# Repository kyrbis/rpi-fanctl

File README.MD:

This is a replacement pcb for the [ElectroCookie Raspberry Pi 4 Case, Aluminum Mini Tower Case](https://www.amazon.de/dp/B09R6TZCQ8) (or probably [this one](https://www.amazon.de/dp/B09QG349ZL)) to be used with PWM controlled 5V fans like [noctua NF-A4x10 5V PWM, 4-Pin](https://www.amazon.de/dp/B07DXS86G7).

You might also need a [3D printed fan adapter](https://www.thingiverse.com/thing:2995904).

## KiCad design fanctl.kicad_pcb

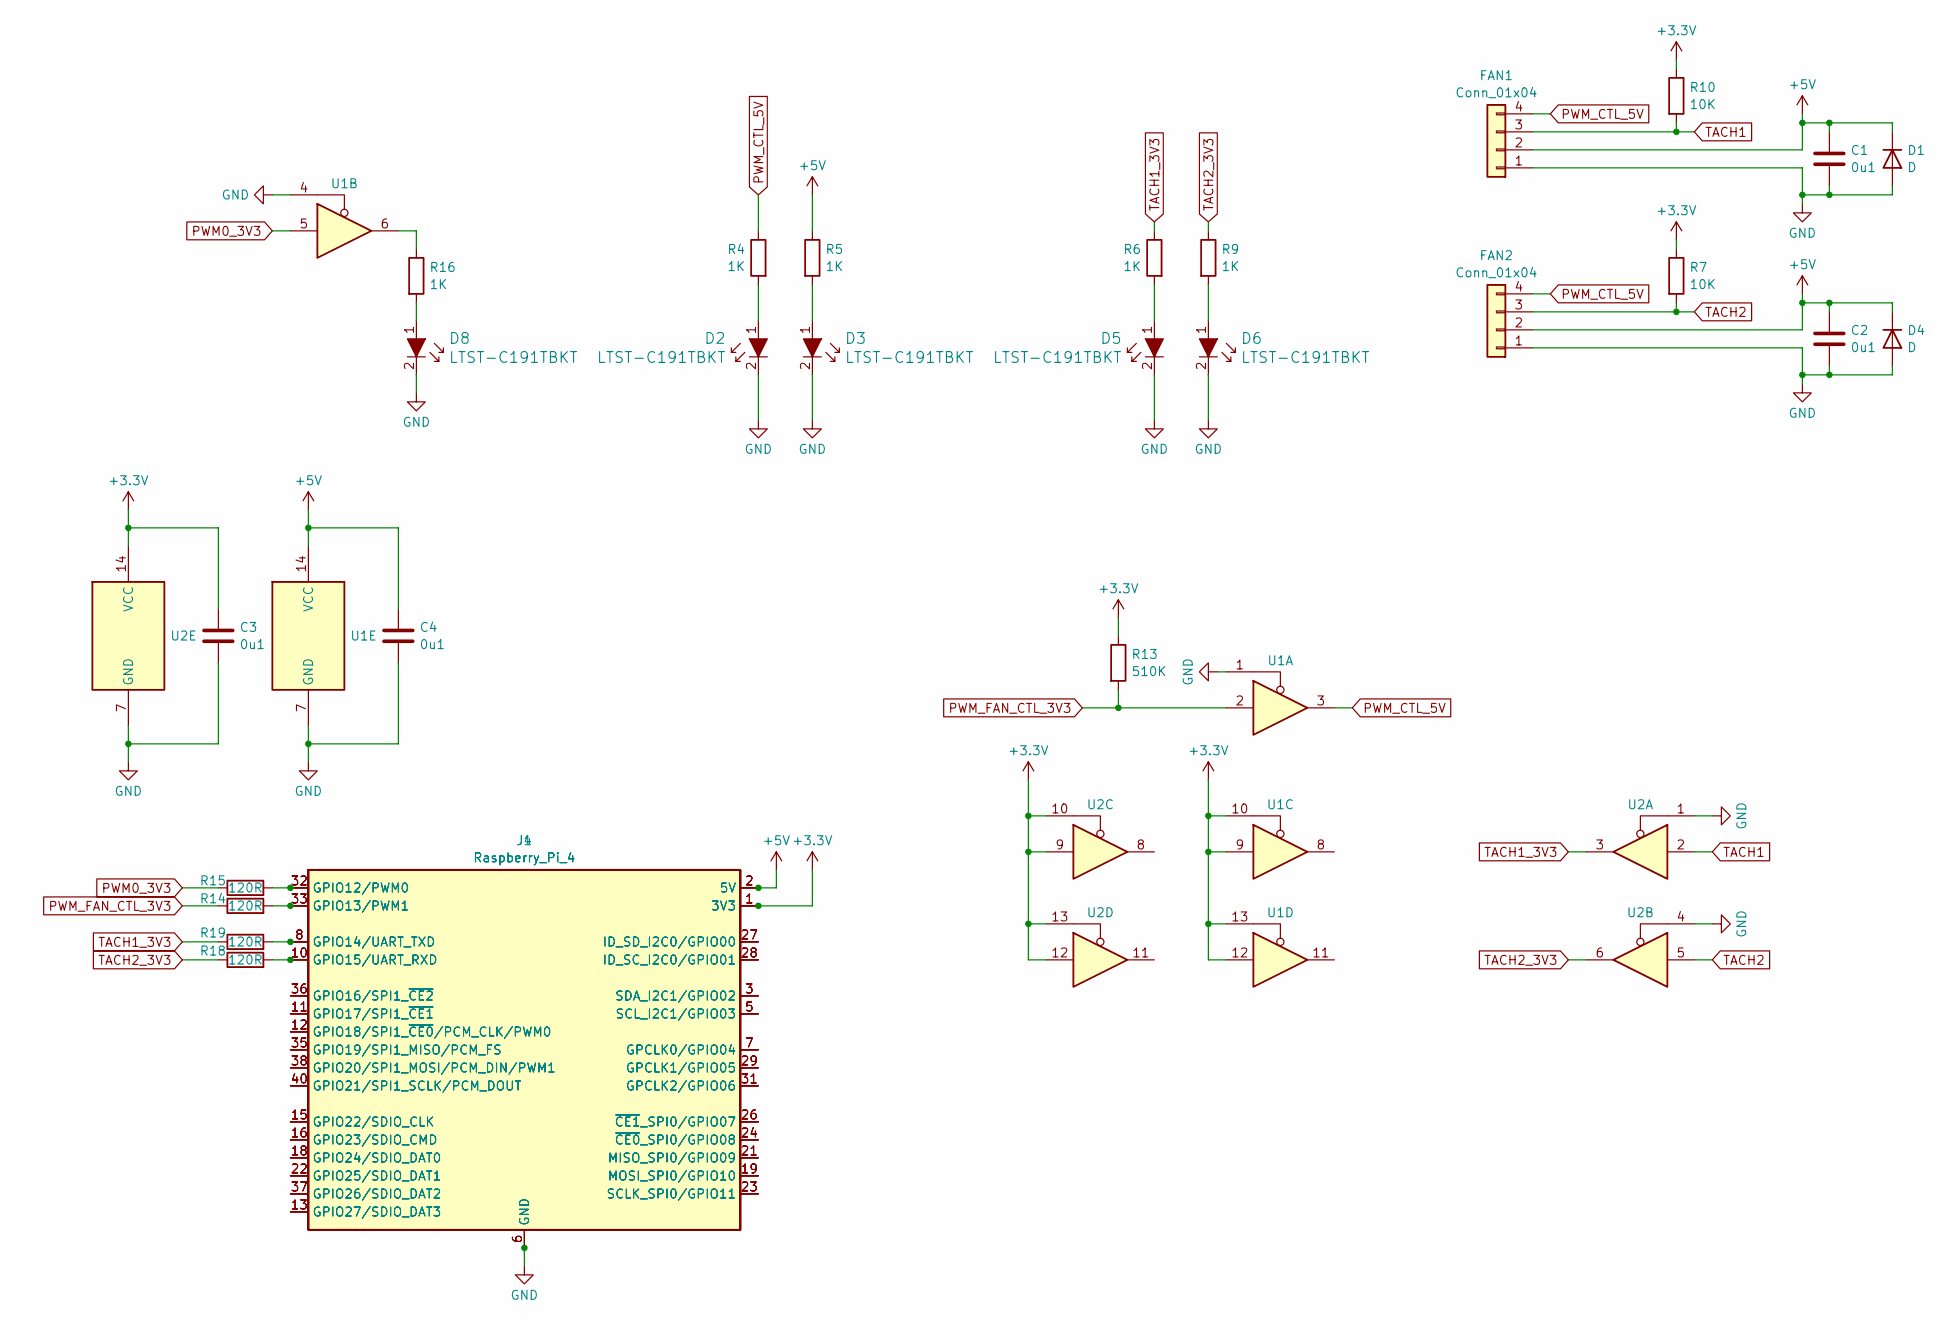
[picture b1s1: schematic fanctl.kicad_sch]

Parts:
C1, C2, C3, C4: 0u1; C_0805_2012Metric
D1: D; D_SOD-123F
D2, D3, D5, D6, D8: LTST-C191TBKT; D_0402_1005Metric_Pad0.77x0.64mm_HandSolder; MPN LTST-C191TBKT; Digi-Key_PN 160-1647-1-ND
D4: D; D_SOD-123
FAN1, FAN2: Conn_01x04; PinHeader_1x04_P2.54mm_Horizontal
J1: Raspberry_Pi_4; PinSocket_2x20_P2.54mm_Horizontal
J4: Raspberry_Pi_4; PinHeader_2x20_P2.54mm_Vertical
R4, R5, R6, R9, R16: 1K; R_0603_1608Metric_Pad0.98x0.95mm_HandSolder
R7, R10: 10K; R_0603_1608Metric_Pad0.98x0.95mm_HandSolder
R13: 510K; R_0603_1608Metric_Pad0.98x0.95mm_HandSolder
R14, R15, R18, R19: 120R; R_0603_1608Metric_Pad0.98x0.95mm_HandSolder
U1, U2: SN74HCT125DR; SOIC-14_3.9x8.7mm_P1.27mm

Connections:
+3.3V: C3.1, J1.1 (3V3), J1.17 (3V3), J4.1 (3V3), J4.17 (3V3), R7.1, R10.1, R13.1, U1.9, U1.10, U1.12, U1.13, U2.9, U2.10, U2.12, U2.13, U2.14 (VCC)
+5V: C1.1, C2.1, C4.1, D1.1 (K), D4.1 (K), FAN1.2, FAN2.2, J1.2 (5V), J1.4 (5V), J4.2 (5V), J4.4 (5V), R5.1, U1.14 (VCC)
GND: C1.2, C2.2, C3.2, C4.2, D1.2 (A), D2.2, D3.2, D4.2 (A), D5.2, D6.2, D8.2, FAN1.1, FAN2.1, J1.6 (GND), J1.9 (GND), J1.14 (GND), J1.20 (GND), J1.25 (GND), J1.30 (GND), J1.34 (GND), J1.39 (GND), J4.6 (GND), J4.9 (GND), J4.14 (GND), J4.20 (GND), J4.25 (GND), J4.30 (GND), J4.34 (GND), J4.39 (GND), U1.1, U1.4, U1.7 (GND), U2.1, U2.4, U2.7 (GND)
unnamed: D2.1, R4.2
unnamed: D3.1, R5.2
unnamed: D5.1, R6.2
unnamed: D6.1, R9.2
unnamed: D8.1, R16.2
unnamed: J1.7 (GPCLK0/GPIO04), J4.7 (GPCLK0/GPIO04)
unnamed: J1.29 (GPCLK1/GPIO05), J4.29 (GPCLK1/GPIO05)
unnamed: J1.31 (GPCLK2/GPIO06), J4.31 (GPCLK2/GPIO06)
unnamed: J1.32 (GPIO12/PWM0), J4.32 (GPIO12/PWM0), R15.2
unnamed: J1.33 (GPIO13/PWM1), J4.33 (GPIO13/PWM1), R14.2
unnamed: J1.8 (GPIO14/UART_TXD), J4.8 (GPIO14/UART_TXD), R19.2
unnamed: J1.10 (GPIO15/UART_RXD), J4.10 (GPIO15/UART_RXD), R18.2
unnamed: J1.36 (GPIO16/SPI1_~CE2), J4.36 (GPIO16/SPI1_~CE2)
unnamed: J1.11 (GPIO17/SPI1_~CE1), J4.11 (GPIO17/SPI1_~CE1)
unnamed: J1.12 (GPIO18/SPI1_~CE0/PCM_CLK/PWM0), J4.12 (GPIO18/SPI1_~CE0/PCM_CLK/PWM0)
unnamed: J1.35 (GPIO19/SPI1_MISO/PCM_FS), J4.35 (GPIO19/SPI1_MISO/PCM_FS)
unnamed: J1.38 (GPIO20/SPI1_MOSI/PCM_DIN/PWM1), J4.38 (GPIO20/SPI1_MOSI/PCM_DIN/PWM1)
unnamed: J1.40 (GPIO21/SPI1_SCLK/PCM_DOUT), J4.40 (GPIO21/SPI1_SCLK/PCM_DOUT)
unnamed: J1.15 (GPIO22/SDIO_CLK), J4.15 (GPIO22/SDIO_CLK)
unnamed: J1.16 (GPIO23/SDIO_CMD), J4.16 (GPIO23/SDIO_CMD)
unnamed: J1.18 (GPIO24/SDIO_DAT0), J4.18 (GPIO24/SDIO_DAT0)
unnamed: J1.22 (GPIO25/SDIO_DAT1), J4.22 (GPIO25/SDIO_DAT1)
unnamed: J1.37 (GPIO26/SDIO_DAT2), J4.37 (GPIO26/SDIO_DAT2)
unnamed: J1.13 (GPIO27/SDIO_DAT3), J4.13 (GPIO27/SDIO_DAT3)
unnamed: J1.28 (ID_SC_I2C0/GPIO01), J4.28 (ID_SC_I2C0/GPIO01)
unnamed: J1.27 (ID_SD_I2C0/GPIO00), J4.27 (ID_SD_I2C0/GPIO00)
unnamed: J1.21 (MISO_SPI0/GPIO09), J4.21 (MISO_SPI0/GPIO09)
unnamed: J1.19 (MOSI_SPI0/GPIO10), J4.19 (MOSI_SPI0/GPIO10)
unnamed: J1.23 (SCLK_SPI0/GPIO11), J4.23 (SCLK_SPI0/GPIO11)
unnamed: J1.5 (SCL_I2C1/GPIO03), J4.5 (SCL_I2C1/GPIO03)
unnamed: J1.3 (SDA_I2C1/GPIO02), J4.3 (SDA_I2C1/GPIO02)
unnamed: J1.24 (~CE0_SPI0/GPIO08), J4.24 (~CE0_SPI0/GPIO08)
unnamed: J1.26 (~CE1_SPI0/GPIO07), J4.26 (~CE1_SPI0/GPIO07)
unnamed: R16.1, U1.6
PWM0_3V3: R15.1, U1.5
PWM_CTL_5V: FAN1.4, FAN2.4, R4.1, U1.3
PWM_FAN_CTL_3V3: R13.2, R14.1, U1.2
TACH1: FAN1.3, R10.2, U2.2
TACH1_3V3: R6.1, R19.1, U2.3
TACH2: FAN2.3, R7.2, U2.5
TACH2_3V3: R9.1, R18.1, U2.6

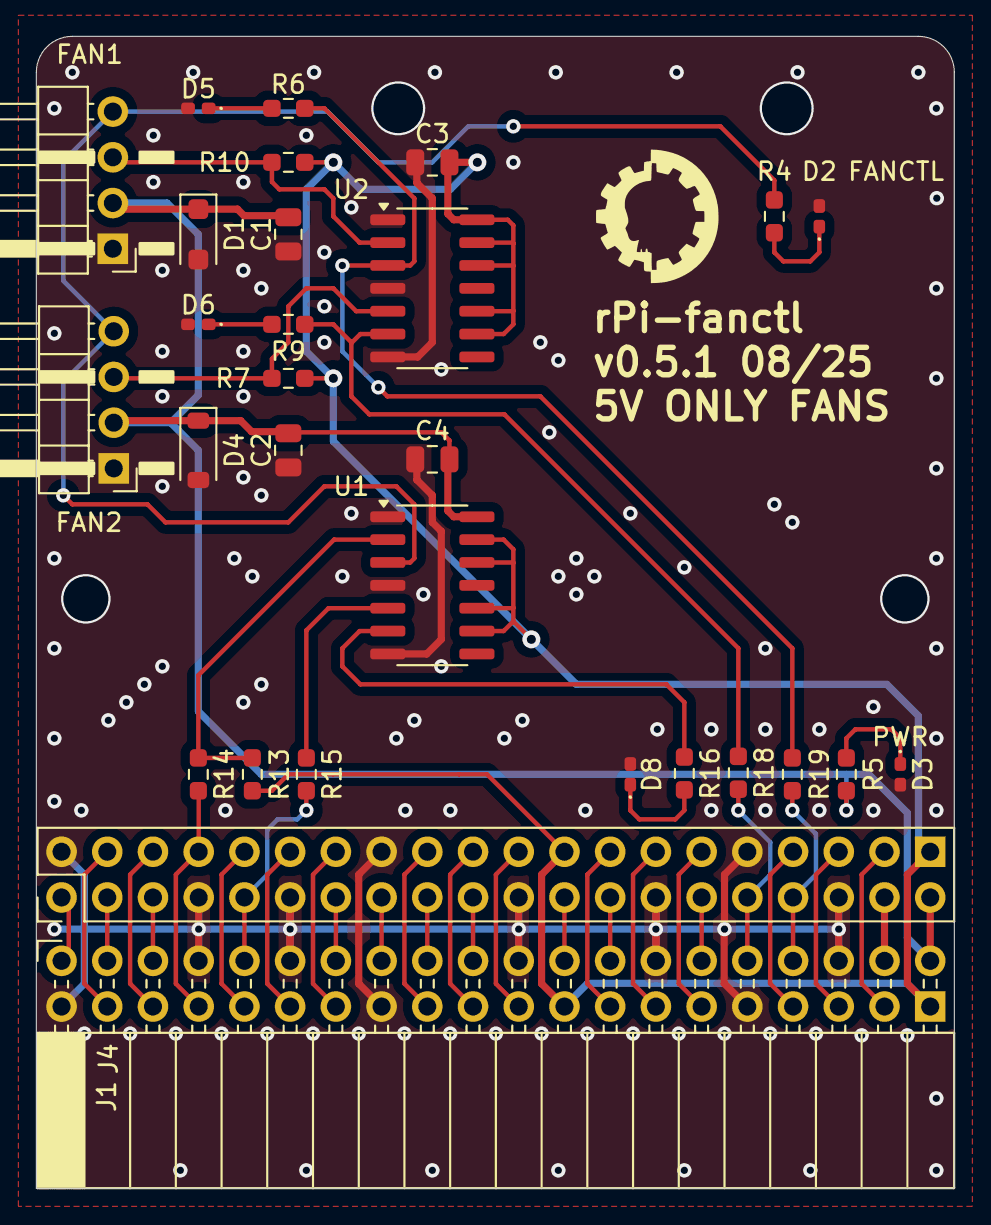
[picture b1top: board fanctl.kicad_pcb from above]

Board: 4 copper layers, 51.0 x 64.0 mm, 29 parts (0 on the bottom side), 44 nets.

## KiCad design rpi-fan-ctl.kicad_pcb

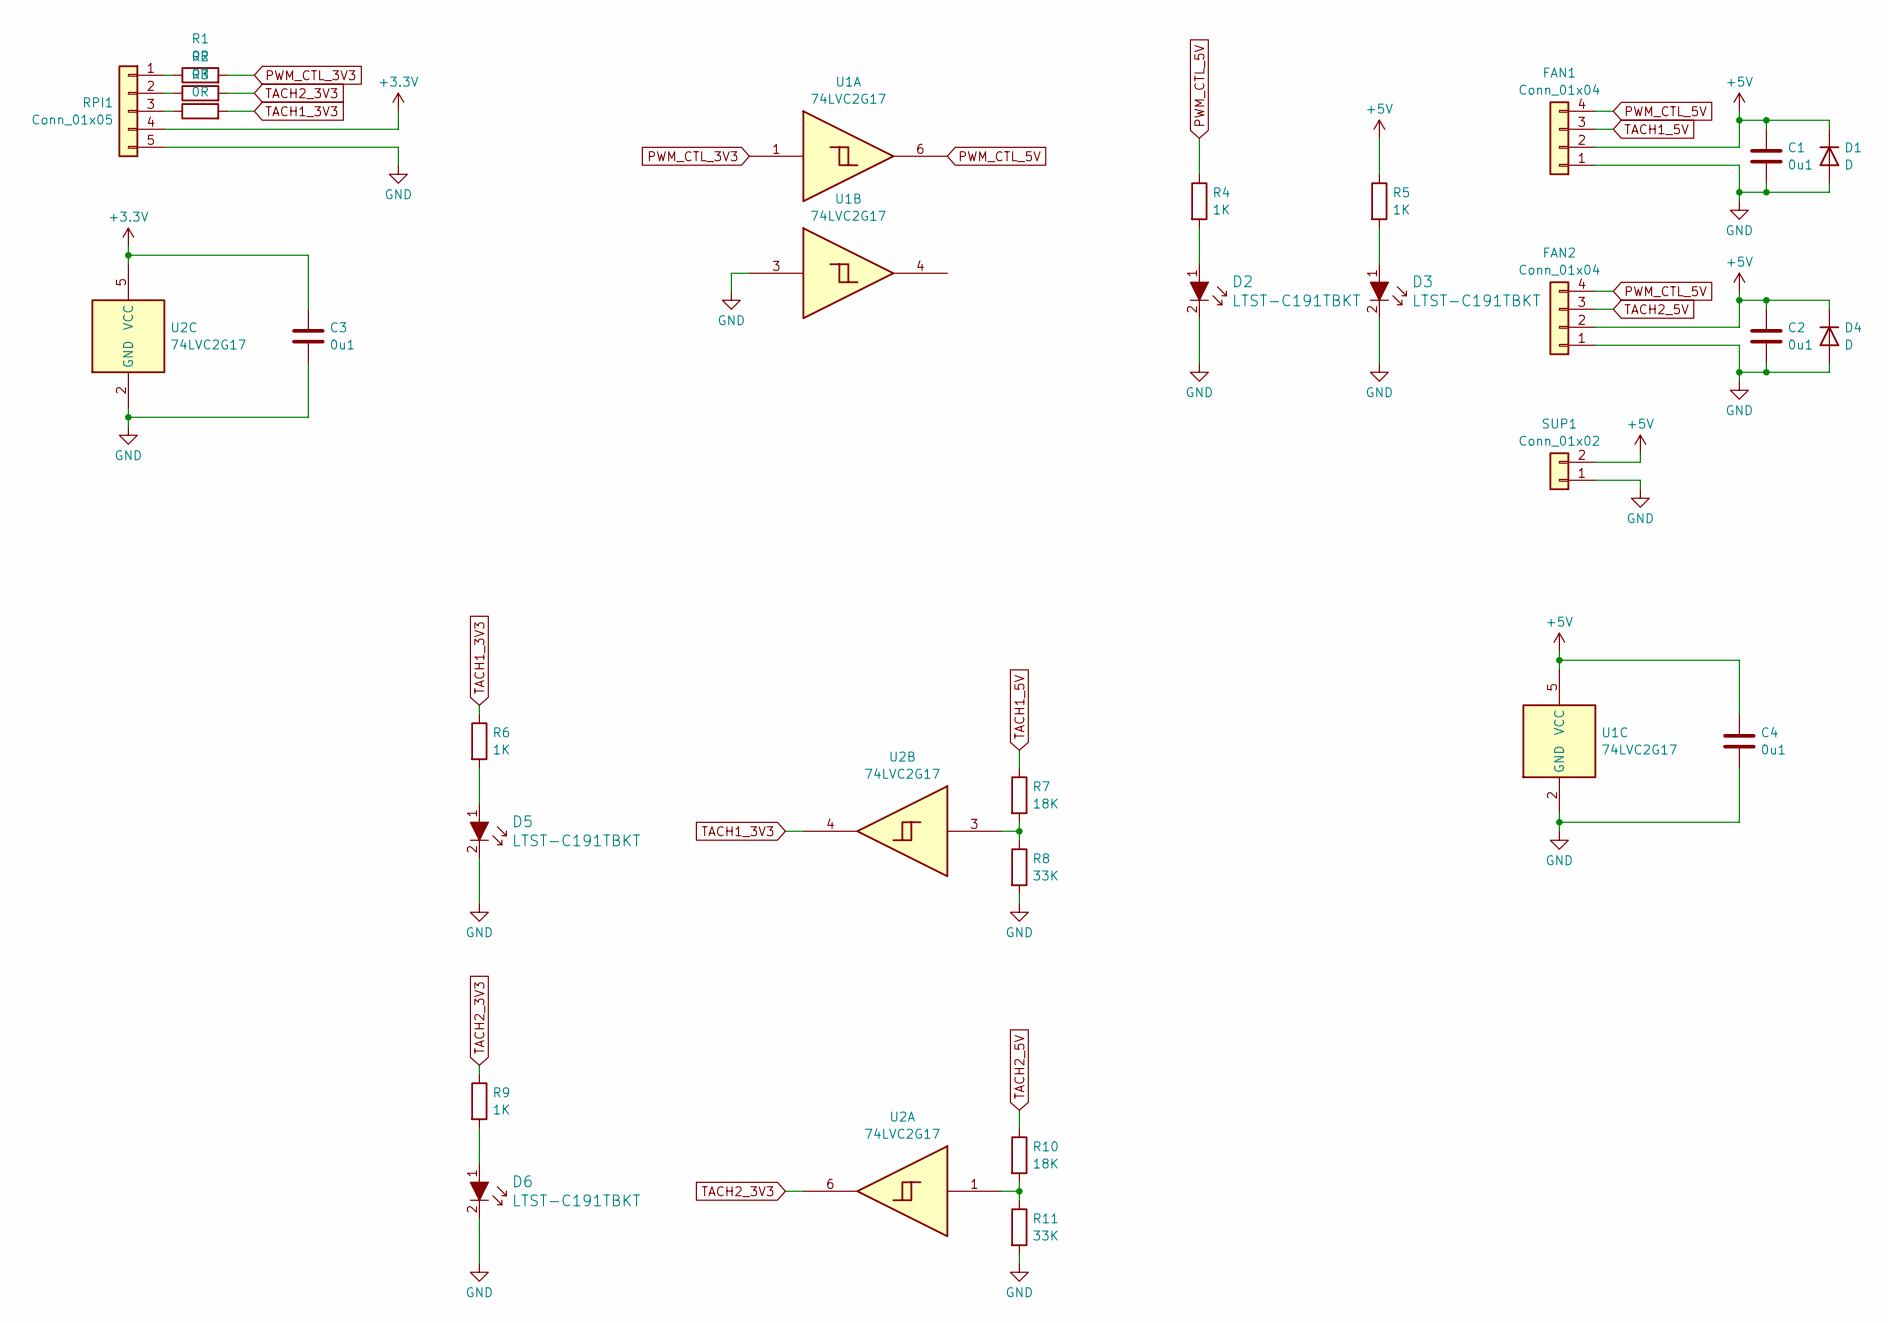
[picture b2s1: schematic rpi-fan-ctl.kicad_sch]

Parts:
C1, C2, C3, C4: 0u1; C_0603_1608Metric_Pad1.08x0.95mm_HandSolder
D1: D; D_SOD-123F
D2, D3, D5, D6: LTST-C191TBKT; D_0402_1005Metric_Pad0.77x0.64mm_HandSolder; MPN LTST-C191TBKT; Digi-Key_PN 160-1647-1-ND
D4: D; D_SOD-123
FAN1, FAN2: Conn_01x04; PinHeader_1x04_P2.54mm_Horizontal
R1, R2, R3: 0R; R_0603_1608Metric_Pad0.98x0.95mm_HandSolder
R4, R5, R6, R9: 1K; R_0603_1608Metric_Pad0.98x0.95mm_HandSolder
R7, R10: 18K; R_0603_1608Metric_Pad0.98x0.95mm_HandSolder
R8, R11: 33K; R_0603_1608Metric_Pad0.98x0.95mm_HandSolder
RPI1: Conn_01x05; PinHeader_1x05_P2.54mm_Horizontal
SUP1: Conn_01x02; PinHeader_1x02_P2.54mm_Horizontal
U1, U2: 74LVC2G17; SOT-23-6_Handsoldering

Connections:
+3.3V: C3.1, RPI1.4, U2.5 (VCC)
+5V: C1.1, C2.1, C4.1, D1.1 (K), D4.1 (K), FAN1.2, FAN2.2, R5.1, SUP1.2, U1.5 (VCC)
GND: C1.2, C2.2, C3.2, C4.2, D1.2 (A), D2.2, D3.2, D4.2 (A), D5.2, D6.2, FAN1.1, FAN2.1, R8.2, R11.2, RPI1.5, SUP1.1, U1.2 (GND), U1.3, U2.2 (GND)
unnamed: D2.1, R4.2
unnamed: D3.1, R5.2
unnamed: D5.1, R6.2
unnamed: D6.1, R9.2
unnamed: R7.2, R8.1, U2.3
unnamed: R10.2, R11.1, U2.1
unnamed: R1.1, RPI1.1
unnamed: R2.1, RPI1.2
unnamed: R3.1, RPI1.3
PWM_CTL_3V3: R1.2, U1.1
PWM_CTL_5V: FAN1.4, FAN2.4, R4.1, U1.6
TACH1_3V3: R3.2, R6.1, U2.4
TACH1_5V: FAN1.3, R7.1
TACH2_3V3: R2.2, R9.1, U2.6
TACH2_5V: FAN2.3, R10.1

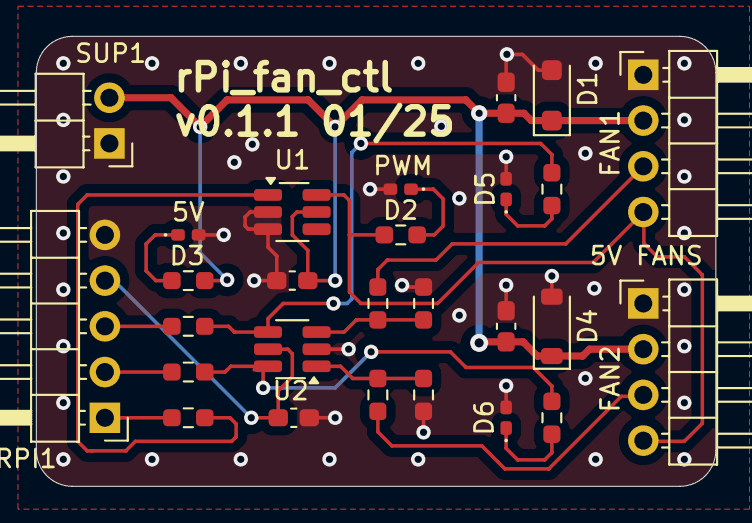
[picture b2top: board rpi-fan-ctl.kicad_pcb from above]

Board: 4 copper layers, 37.8 x 25.0 mm, 27 parts (0 on the bottom side), 18 nets.

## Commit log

2025-01-08 added footprints
2025-01-08 some routing progress
2025-01-08 finish?
2025-01-08 made all preview connectors angled
2025-01-14 updated voltage level converter
2025-01-14 file naming refactor
2025-01-14 WIP preview sch
2025-01-18 release candidate
2025-01-18 review feedback
2025-01-19 README.MD
2025-02-02 rotated pin headers so they are actually right
2025-02-03 connectors corrected
2025-02-03 added lines to align fan connector
2025-03-03 pcb review from @lukekaese
    much thanks!
2025-03-03 updated preview image
2025-08-10 updated connector yet again (previous versions will not work)
2025-08-10 pcb version bump
